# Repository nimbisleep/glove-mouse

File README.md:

#  Glove Mouse — Wireless Gesture-Controlled HID

**Graduation Project (Bitirme)** — Düzce University, EEE Department

A wireless glove mouse controlled by hand gestures. Uses an **ESP32** with **MPU6050 IMU (DMP)** for drift-free cursor tracking over **Bluetooth BLE**. No receiver dongle needed — pairs like any standard Bluetooth mouse.

---

##  Features

- **Drift-free cursor** — MPU6050 DMP (Digital Motion Processor) handles all orientation math on-chip. Pitch moves cursor up/down, roll moves left/right. No accumulated drift.
- **Bluetooth BLE** — ESP32 built-in BLE, pairs natively with Windows, macOS, Linux, Android
- **3 Modes:**
  - **Fix** — cursor locked in place (thumb capacitive touch)
  - **Air Tap** — capacitive trigger for click
  - **Inactive** — hand resting, no cursor movement
- **Adjustable sensitivity** — dynamic deadzone filtering
- **Custom PCB** — KiCad-designed, LTspice-validated
- **Battery-powered** — portable, wearable form factor

---

## 📁 Repository Structure

```
glove-mouse/
├── firmware/                  # ESP32 Arduino firmware
│   ├── glove_mouse_v5.ino     # Latest — DMP-based, gravity anchored
│   ├── glove_mouse_dmp.ino    # DMP firmware variant
│   ├── GloveMouse_Movement.ino
│   ├── glove_mouse_final.ino
│   ├── glove_mouse_v4.ino
│   ├── glove_mouse_v3.ino
│   └── glove_mouse_v2.ino
├── hardware/
│   └── schematics/            # KiCad PCB design files
│       ├── schematics.kicad_pcb    # PCB layout
│       ├── schematics.kicad_sch    # Schematic
│       ├── schematics.kicad_pro    # Project file
│       └── *.gbr                  # Gerber files for fabrication
└── README.md
```

---

##  Hardware

| Component | Purpose |
|-----------|---------|
| ESP32 WROOM | Main MCU + BLE |
| MPU6050 | 6-axis IMU with DMP |
| TTP223 | Capacitive touch for click/mode |
| Flex sensors (x5) | Finger bend detection (WIP) |
| Custom PCB | KiCad-designed 2-layer board |

---

##  Firmware

The firmware uses the MPU6050's built-in DMP (Digital Motion Processor) to get stable, drift-free orientation data. The ESP32 handles BLE HID mouse reporting.

**Key firmware files:**
- `glove_mouse_v5.ino` — Latest version. Uses gravity-anchored pitch/roll, no yaw (drifts). Includes sensitivity tuning.
- `glove_mouse_dmp.ino` — DMP implementation with raw quaternion output.

### Wiring
```
MPU6050 VCC  → ESP32 3.3V
MPU6050 GND  → ESP32 GND
MPU6050 SDA  → ESP32 GPIO 21
MPU6050 SCL  → ESP32 GPIO 22
MPU6050 INT  → ESP32 GPIO 19
MPU6050 AD0  → GND
```

### Required Libraries
- `MPU6050` by ElectronicCats
- ESP32 BLE (built into ESP32 Arduino core)

---

##  PCB (KiCad)

The custom PCB is designed in KiCad as a 2-layer board:
- ESP32 footprint with all required passives
- MPU6050 IMU with I2C pull-ups and decoupling
- TTP223 capacitive touch pad
- Battery management circuit
- Breakout headers for flex sensors

Gerber files (`*.gbr`) are included for direct fabrication.

---

##  Status

| Component | Status |
|-----------|--------|
| ✅ Movement tracking | Working via BLE |
| ✅ Click/gesture logic | Implemented |
| ✅ KiCad PCB | Designed |
| ✅ Flex sensors | Added |
| ✅ Final assembly | Glove mounting + battery |

---

##  Contact

**Salah Hussein Osman**  
saalahsega01@gmail.com

---

*Presented at Düzce University Bitirme Projeleri Sunum ve Poster Sergisi — 21 May 2026*

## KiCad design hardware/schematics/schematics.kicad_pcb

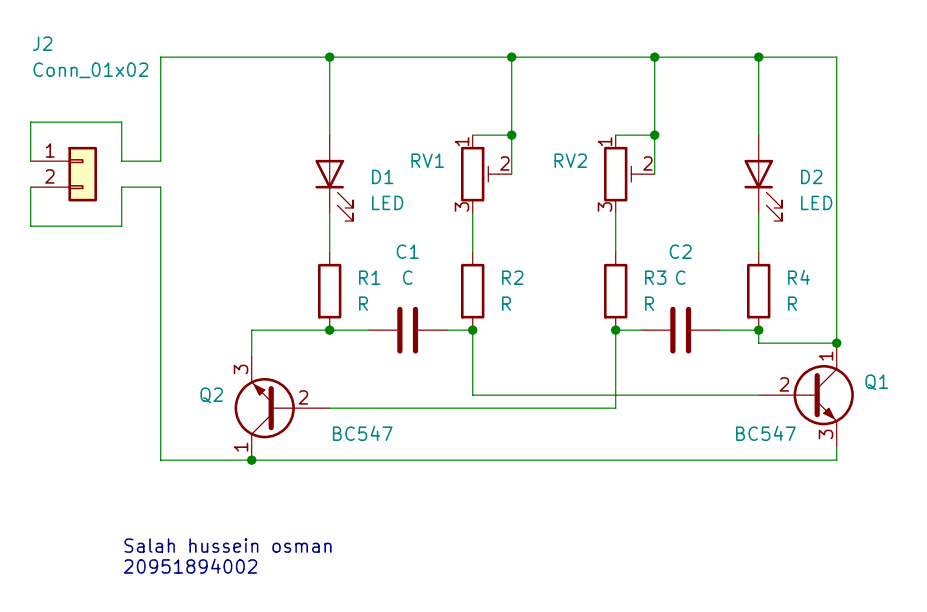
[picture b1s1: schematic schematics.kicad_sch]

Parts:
C1, C2: C; CP_Radial_D6.3mm_P2.50mm
D1, D2: LED; LED_D5.0mm
J2: Conn_01x02; TerminalBlock_bornier-2_P5.08mm
Q1, Q2: BC547; TO-92L_Inline_Wide
R1, R2, R3, R4: R; R_Axial_DIN0207_L6.3mm_D2.5mm_P10.16mm_Horizontal
RV1, RV2: R_Potentiometer_Trim; Potentiometer_Bourns_3386F_Vertical

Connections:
unnamed: C2.2, D1.2 (A), D2.2 (A), J2.1, Q1.1 (C), R4.2, RV1.1, RV1.2, RV2.1, RV2.2
unnamed: D1.1 (K), R1.1
unnamed: D2.1 (K), R4.1
unnamed: J2.2, Q1.3 (E), Q2.1 (C)
unnamed: C1.2, Q1.2 (B), R2.2
unnamed: C2.1, Q2.2 (B), R3.2
unnamed: C1.1, Q2.3 (E), R1.2
unnamed: R2.1, RV1.3
unnamed: R3.1, RV2.3

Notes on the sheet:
Salah hussein osman 20951894002

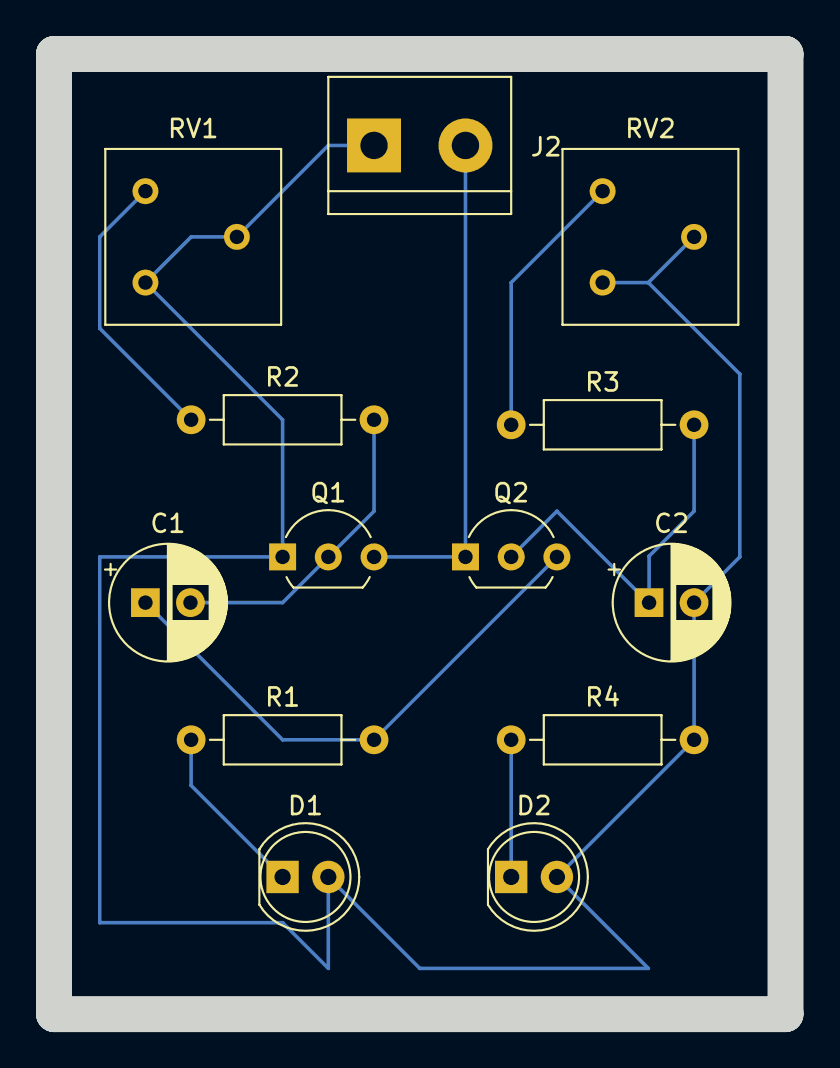
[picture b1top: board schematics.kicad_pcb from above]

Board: 2 copper layers, 40.6 x 53.3 mm, 13 parts (0 on the bottom side), 9 nets.

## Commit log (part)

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2026-03-06 Enhance README with project details in English and Turkish
    Added detailed project description, functionality, components, and status in both English and Turkish.
2026-05-13 Add proper README and .gitignore
2026-05-13 Add firmware (ESP32 .ino), KiCad PCB schematics & Gerber files, update README
